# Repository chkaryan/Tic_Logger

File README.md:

# Tic_Logger
Master folder for my Bachelor's Degree thesis research on a wearable device that predicts if a sudden movement was a tic or not with the help of LSTM, a Deep Learning algorithm

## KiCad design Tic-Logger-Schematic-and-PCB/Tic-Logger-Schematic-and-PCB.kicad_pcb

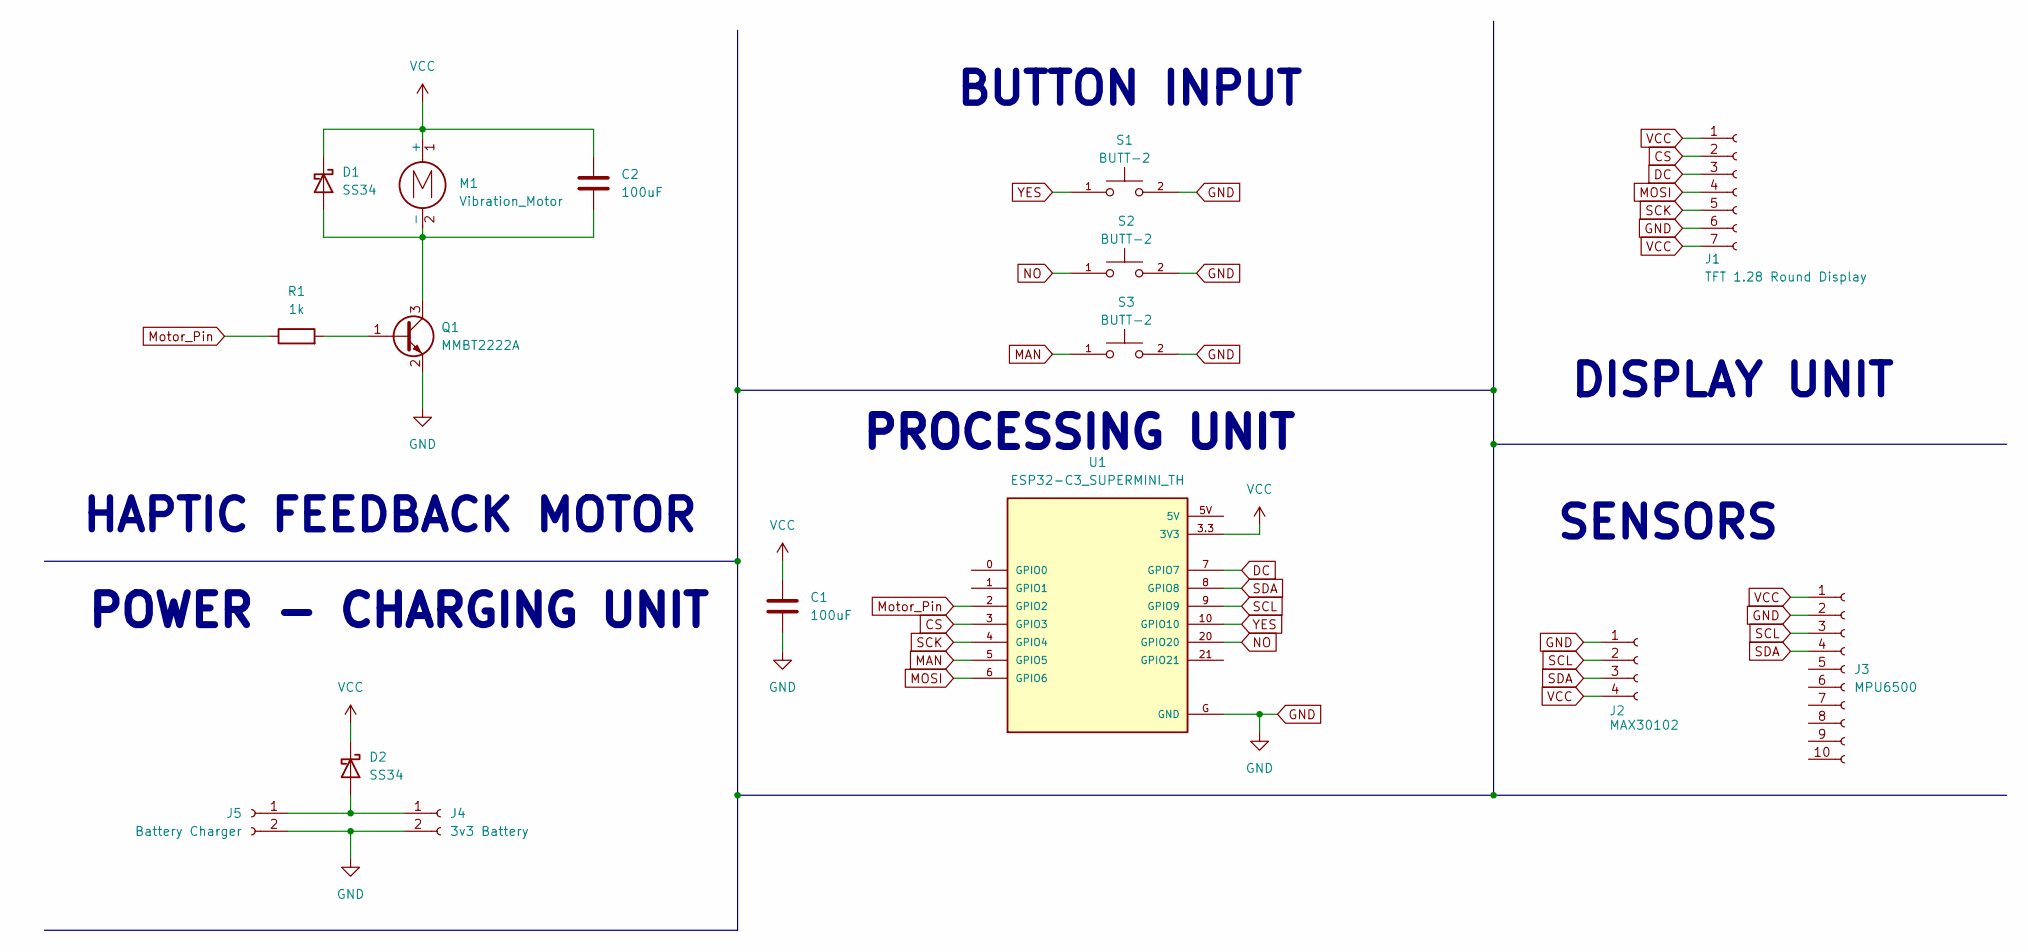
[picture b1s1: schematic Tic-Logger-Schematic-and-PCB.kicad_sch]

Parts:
C1, C2: 100uF; C_1206_3216Metric
D1, D2: SS34; D_SMA
J1: TFT 1.28 Round Display; PinSocket_1x07_P2.54mm_Vertical
J2: MAX30102; PinSocket_1x04_P2.54mm_Vertical
J3: MPU6500; PinSocket_1x10_P2.54mm_Vertical
J4: 3v3 Battery; JST_PH_B2B-PH-K_1x02_P2.00mm_Vertical
J5: Battery Charger; JST_PH_B2B-PH-K_1x02_P2.00mm_Vertical
M1: Vibration_Motor; PinHeader_1x02_P2.54mm_Vertical
Q1: MMBT2222A; SOT-23
R1: 1k; R_1206_3216Metric
S1, S2, S3: BUTT-2; SW_BUTT-2; PARTREV N/A
U1: ESP32-C3_SUPERMINI_TH; MODULE_ESP32-C3_SUPERMINI_TH

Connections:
CS: J1.2, U1.3 (GPIO3)
DC: J1.3, U1.7 (GPIO7)
GND: C1.2, J1.6, J2.1, J3.2, J4.2, J5.2, Q1.2 (E), S1.2, S2.2, S3.2, U1.G (GND)
MAN: S3.1, U1.5 (GPIO5)
MOSI: J1.4, U1.6 (GPIO6)
Motor_Pin: R1.1, U1.2 (GPIO2)
NO: S2.1, U1.20 (GPIO20)
unnamed: C2.2, D1.2 (A), M1.2 (-), Q1.3 (C)
unnamed: D2.2 (A), J4.1, J5.1
unnamed: Q1.1 (B), R1.2
SCK: J1.5, U1.4 (GPIO4)
SCL: J2.2, J3.3, U1.9 (GPIO9)
SDA: J2.3, J3.4, U1.8 (GPIO8)
VCC: C1.1, C2.1, D1.1 (K), D2.1 (K), J1.1, J1.7, J2.4, J3.1, M1.1 (+), U1.3.3 (3V3)
YES: S1.1, U1.10 (GPIO10)

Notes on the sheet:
PROCESSING UNIT
POWER - CHARGING UNIT
BUTTON INPUT
DISPLAY UNIT
HAPTIC FEEDBACK MOTOR
SENSORS

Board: 2 copper layers, 16 parts (3 on the bottom side), 15 nets, no tracks yet.

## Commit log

2026-04-13 moving files to repo
2026-04-26 update 2
